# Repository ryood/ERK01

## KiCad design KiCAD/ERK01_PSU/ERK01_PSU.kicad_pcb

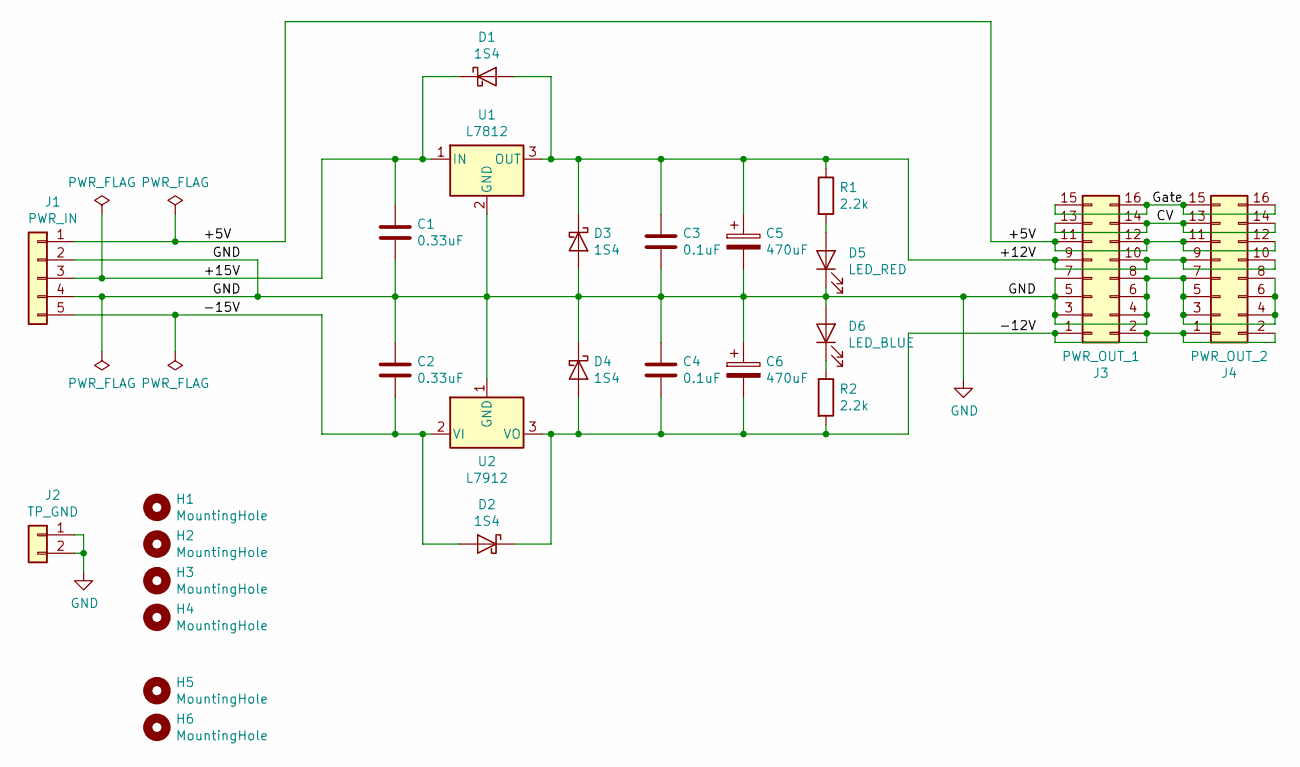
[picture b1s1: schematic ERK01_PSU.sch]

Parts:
C1, C2: 0.33uF; C_Disc_D3.0mm_W1.6mm_P2.50mm
C3, C4: 0.1uF; C_Disc_D3.0mm_W1.6mm_P2.50mm
C5, C6: 470uF; CP_Radial_D10.0mm_P5.00mm
D1, D2, D3, D4: 1S4; D_DO-34_SOD68_P7.62mm_Horizontal
D5: LED_RED; LED_D3.0mm
D6: LED_BLUE; LED_D3.0mm
H1, H2, H3, H4: MountingHole; MountingHole_3.2mm_M3
H5, H6: MountingHole; MountingHole_2.2mm_M2
J1: PWR_IN; JST_XH_B5B-XH-A_1x05_P2.50mm_Vertical
J2: TP_GND; PinHeader_1x02_P2.54mm_Vertical
J3: PWR_OUT_1; IDC-Header_2x08_P2.54mm_Vertical
J4: PWR_OUT_2; IDC-Header_2x08_P2.54mm_Vertical
R1, R2: 2.2k; R_Axial_DIN0207_L6.3mm_D2.5mm_P2.54mm_Vertical
U1: L7812; TO-220-3_Vertical
U2: L7912; TO-220-3_Vertical

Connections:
/+5V: J1.1, J3.11, J3.12, J4.11, J4.12
/+12V: C3.1, C5.1, D1.2 (A), D3.1 (K), J3.9, J3.10, J4.9, J4.10, R1.1, U1.3 (OUT)
/+15V: C1.1, D1.1 (K), J1.3, U1.1 (IN)
/-12V: C4.2, C6.2, D2.1 (K), D4.2 (A), J3.1, J3.2, J4.1, J4.2, R2.2, U2.3 (VO)
/-15V: C2.2, D2.2 (A), J1.5, U2.2 (VI)
/CV: J3.13, J3.14, J4.13, J4.14
/Gate: J3.15, J3.16, J4.15, J4.16
GND: C1.2, C2.1, C3.2, C4.1, C5.2, C6.1, D3.2 (A), D4.1 (K), D5.1 (K), D6.2 (A), J1.2, J1.4, J2.1, J2.2, J3.3, J3.4, J3.5, J3.6, J3.7, J3.8, J4.3, J4.4, J4.5, J4.6, J4.7, J4.8, U1.2 (GND), U2.1 (GND)
unnamed: D5.2 (A), R1.2
unnamed: D6.1 (K), R2.1

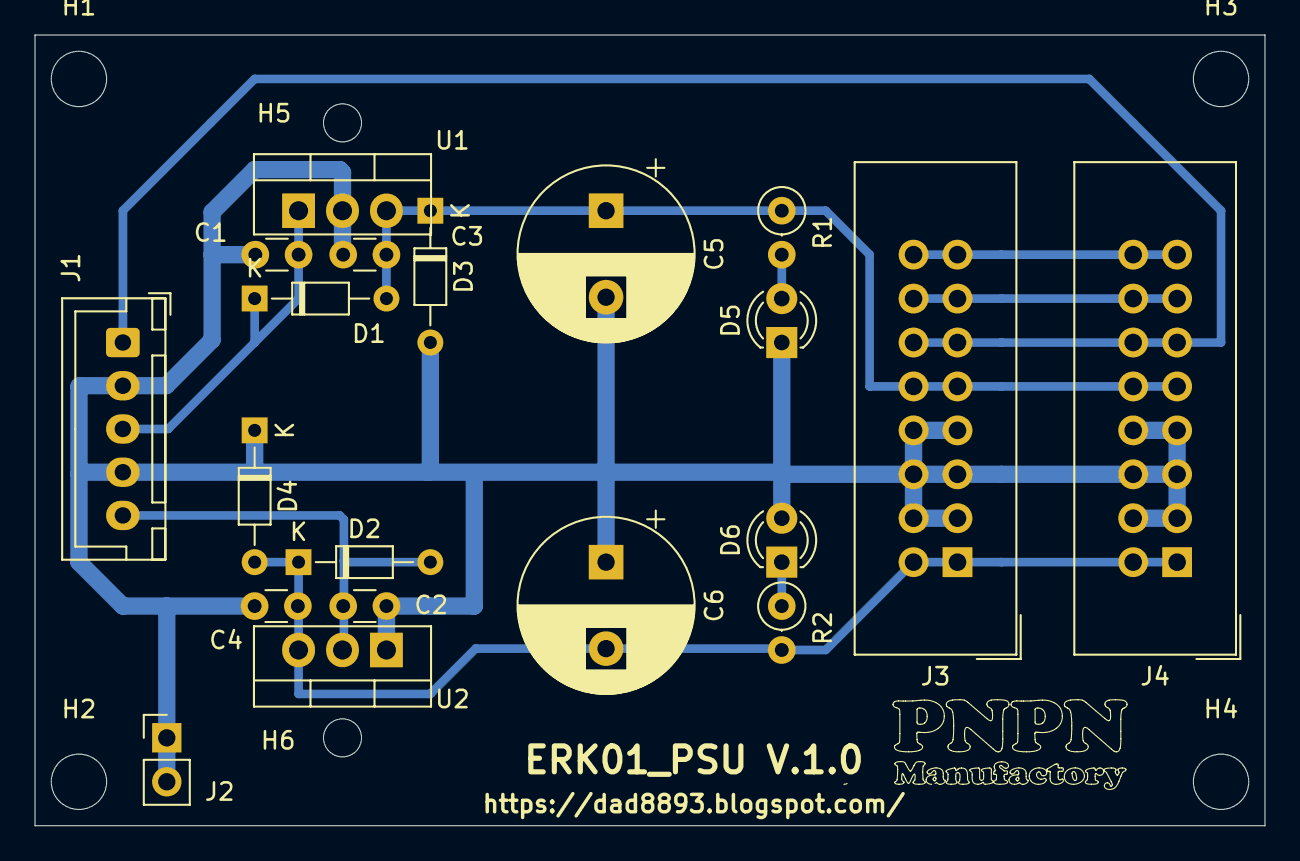
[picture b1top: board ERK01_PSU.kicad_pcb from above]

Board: 2 copper layers, 71.1 x 45.7 mm, 26 parts (0 on the bottom side), 10 nets.

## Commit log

2020-12-11 Add: Panel Size
2020-12-11 Add: Panel Size pdf
2020-12-11 Fix print size
